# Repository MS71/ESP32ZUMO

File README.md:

# ESP32ZUMO
Small robot based on ESP32 + ROS + ZUMO 32u4 base

Components:
* ZUMO32U4 Base (I2C Slave, Bat ADC, Motor Encoder, PWM for Lidar Stepper, l3gd20h, lsm303d, Line Sonsor, ...)
* ESP32 with PSRAM
* STM vl53l1x TOF sensor
* Rotating Lidar with PCF8475+ULN2003 Stepper motor
* BNO055 Orientation Sensor
* SSD1306 I2C Display

Target Software:
* ROS Serial ported to ESP32

Host Software:
* ROS Bringup Files
* Mapping, Laser Scan, Navigation, ...

Goals:
* Small Autonomous Robot controlled by ROS from external PC
* Small Autonomous Robot controlled by ROS running on ESP32

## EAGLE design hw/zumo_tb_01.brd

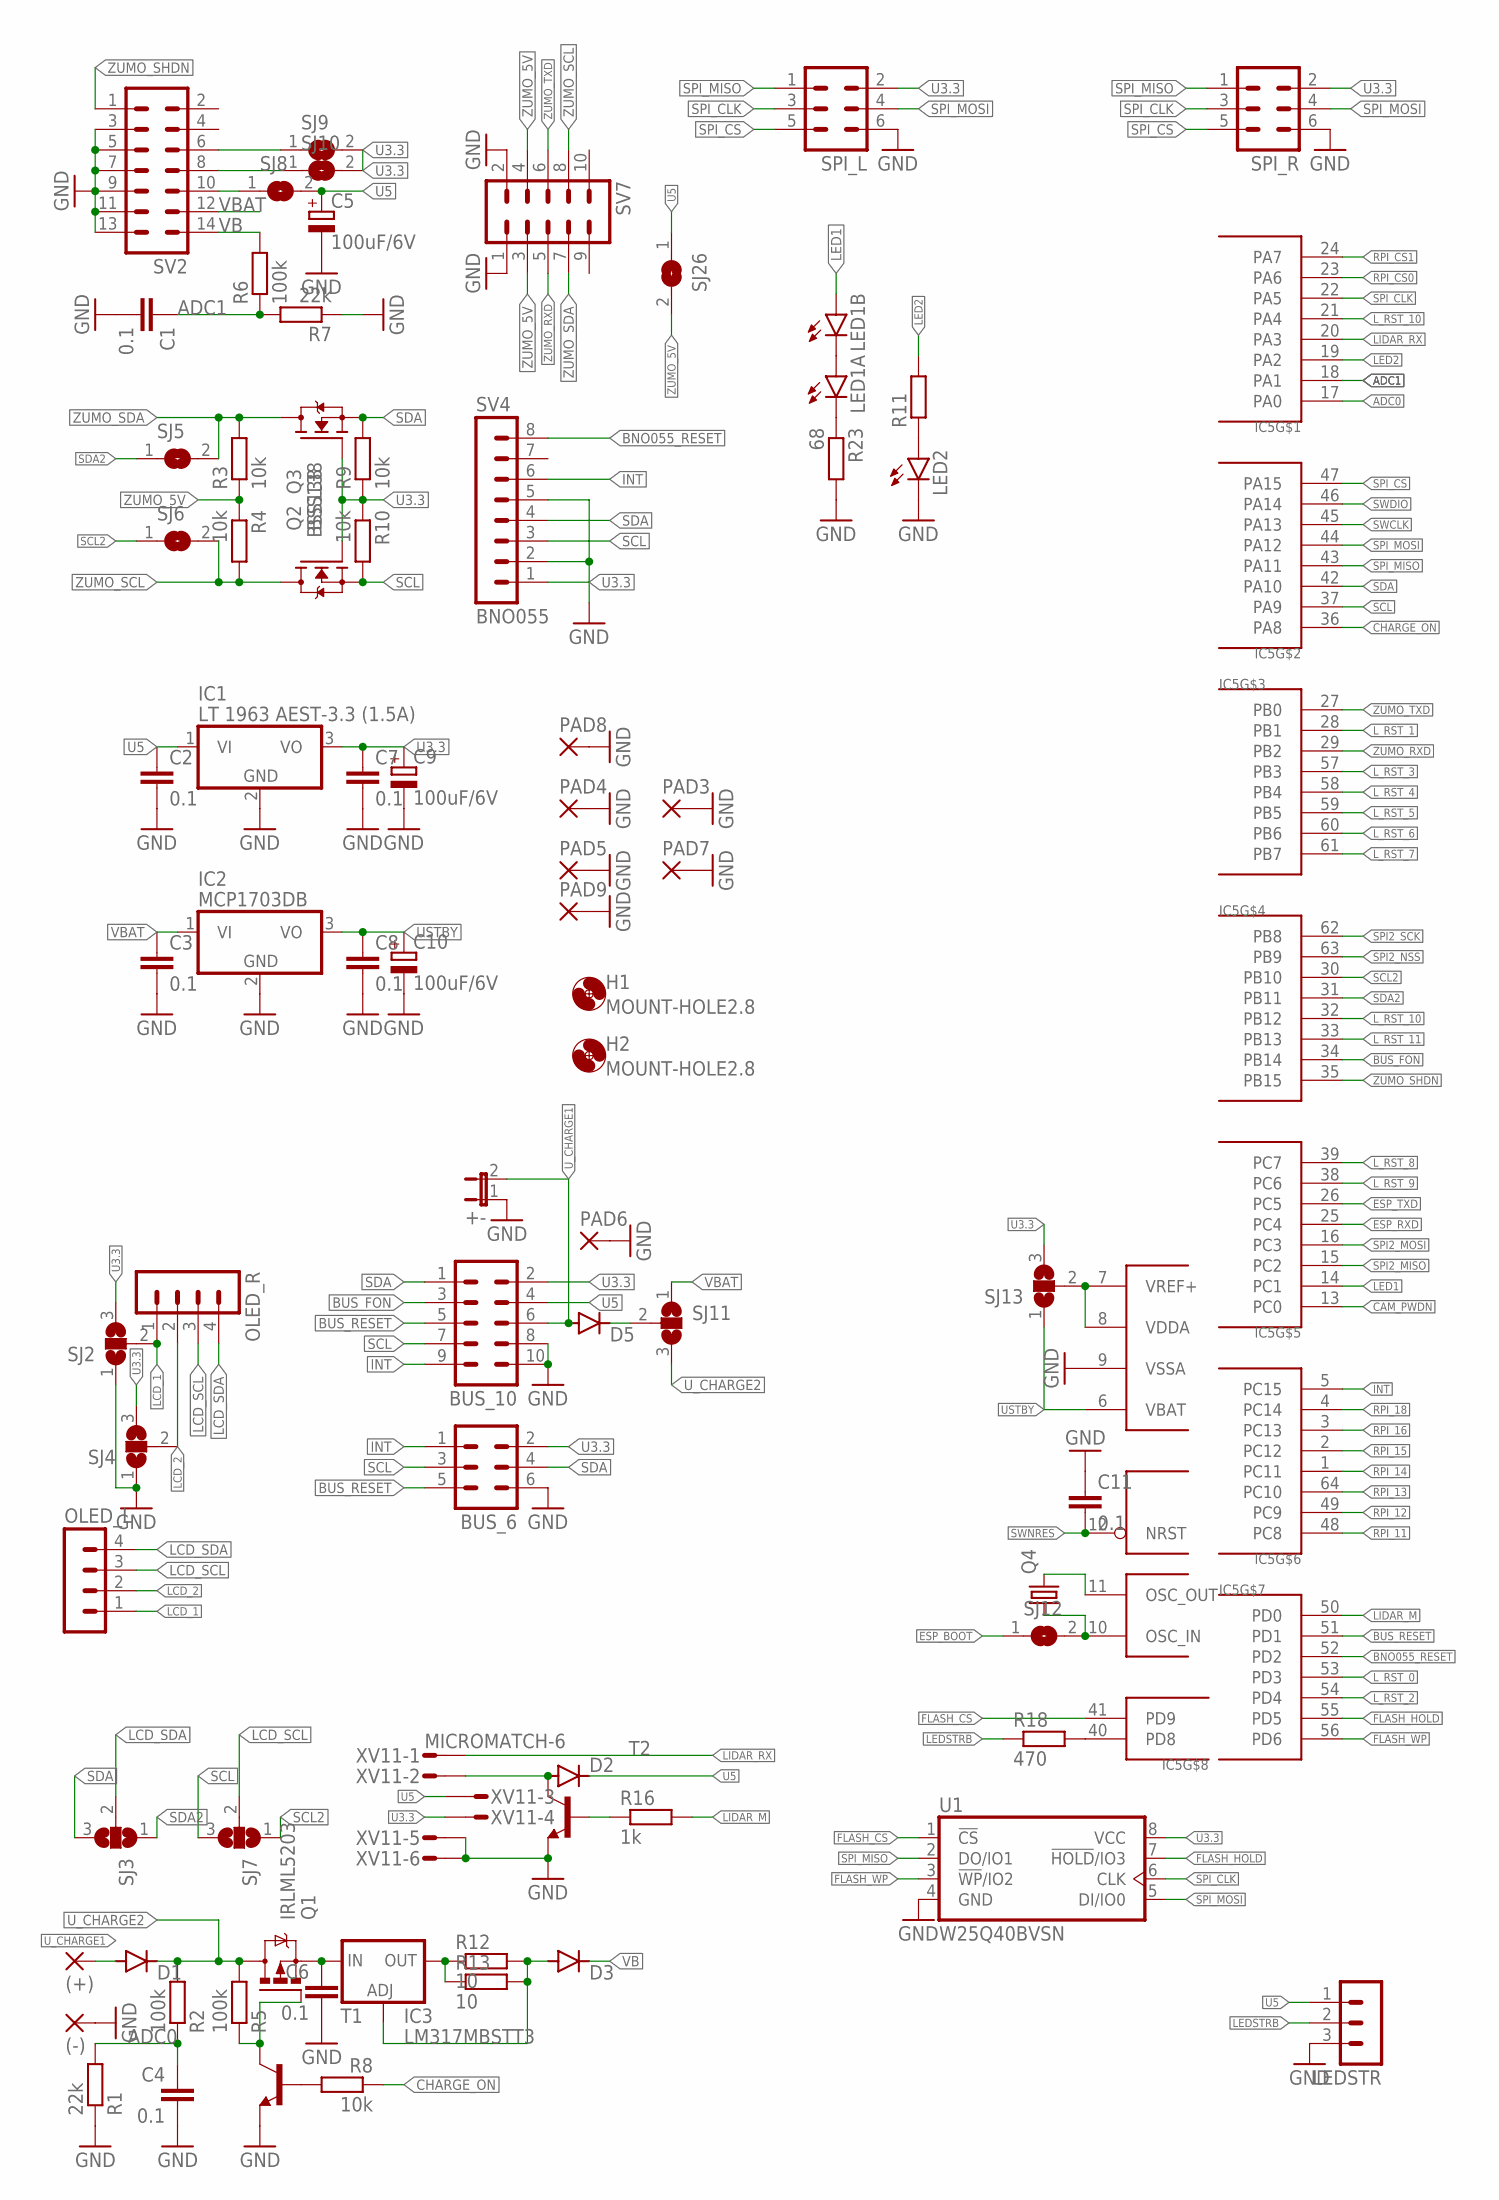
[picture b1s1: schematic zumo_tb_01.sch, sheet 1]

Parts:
(+): 3,81/1,4
(-): 3,81/1,4
+-: JP1E; JP1
BUS_6: ML6
BUS_10: ML10
C1, C2, C3, C4, C6, C7, C8, C11: 0.1; C0805
C5, C9, C10: 100uF/6V; B/3528-21R
D1, D3, D5: DIODE-MELF-MLL41; MELF-MLL41
D2: DIODE-MINIMELF; MINIMELF
H1, H2: MOUNT-HOLE2.8; 2,8
IC1: LT 1963 AEST-3.3 (1.5A); SOT223
IC2: MCP1703DB; SOT223
IC3: LM317MBSTT3; SOT223
IC5: STM32G081RBT6; TQFP64
LED1A, LED1B: LED5MM
LED2: LEDCHIPLED_0805; CHIPLED_0805
LEDSTR: MA03-1
OLED_L: MA04-1
OLED_R: MA04-1
PAD3, PAD7, PAD9: 3,81/1,4
PAD4, PAD5, PAD6, PAD8: 2,15/1,0
Q1: IRLML5203; MICRO3
Q2, Q3: BSS138; SOT23
Q4: CRYSTALTC26V; TC26V
R1, R7: 22k; R0805
R2, R5, R6: 100k; R0805
R3, R4, R8, R9, R10: 10k; R0805
R11: R-EU_R0603; R0603
R12, R13: 10; R2010
R16: 1k; R0805
R18: 470; R0805
R23: 68; R0805
SJ2, SJ3, SJ4, SJ7, SJ11, SJ13: SJ2W; SJ_2
SJ5, SJ6, SJ8, SJ9, SJ10, SJ12, SJ26: SJ
SPI_L: ML6
SPI_R: ML6
SV2: MA07-2
SV4: BNO055; MA08-1
SV7: MA05-2
T1, T2: BC817-16-NPN-SOT23-BEC; SOT23-BEC
U1: W25Q40BVSN; SO08
XV11: MICROMATCH-6

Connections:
ADC0: C4.1, IC5.17 (PA0), R1.2, R2.1
ADC1: C1.1, IC5.18 (PA1), R6.1, R7.2
BNO055_RESET: IC5.52 (PD2), SV4.8
BUS_FON: BUS_10.3, IC5.34 (PB14)
BUS_RESET: BUS_6.5, BUS_10.5, IC5.51 (PD1)
CAM_PWDN: IC5.13 (PC0); also elsewhere on the board
CHARGE_ON: IC5.36 (PA8), R8.1
ESP_BOOT: SJ12.1; also elsewhere on the board
ESP_RXD: IC5.25 (PC4); also elsewhere on the board
ESP_TXD: IC5.26 (PC5); also elsewhere on the board
FLASH_CS: IC5.41 (PD9), U1.1 (!CS!)
FLASH_HOLD: IC5.55 (PD5), U1.7 (!HOLD!/IO3)
FLASH_WP: IC5.56 (PD6), U1.3 (!WP!/IO2)
GND: (-).1, +-.1, BUS_6.6, BUS_10.8, BUS_10.10, C1.2, C2.2, C3.2, C4.2, C5.-, C6.2, C7.2, C8.2, C9.-, C10.-, C11.1, IC1.2 (GND), IC2.2 (GND), IC5.9 (VSSA), LED2.C, LEDSTR.3, PAD3.1, PAD4.1, PAD5.1, PAD6.1, PAD7.1, PAD8.1, PAD9.1, R1.1, R7.1, R23.2, SJ2.1, SJ4.1, SPI_L.6, SPI_R.6, SV2.3, SV2.5, SV2.7, SV2.9, SV2.11, SV2.13, SV4.2, SV4.5, SV7.1, SV7.2, T1.E, T2.E, U1.4 (GND), XV11.5, XV11.6; also elsewhere on the board
INT: BUS_6.1, BUS_10.9, IC5.5 (PC15), SV4.6; also elsewhere on the board
LCD_1: OLED_L.1, OLED_R.1, SJ2.2
LCD_2: OLED_L.2, OLED_R.2, SJ4.2
LCD_SCL: OLED_L.3, OLED_R.3, SJ7.2
LCD_SDA: OLED_L.4, OLED_R.4, SJ3.2
LED1: IC5.14 (PC1), LED1B.A
LED2: IC5.19 (PA2), R11.2
LEDSTRB: LEDSTR.2, R18.1
LIDAR_M: IC5.50 (PD0), R16.2
LIDAR_RX: IC5.20 (PA3), XV11.1
L_RST_0: IC5.53 (PD3); also elsewhere on the board
L_RST_1: IC5.28 (PB1); also elsewhere on the board
L_RST_2: IC5.54 (PD4); also elsewhere on the board
L_RST_3: IC5.57 (PB3); also elsewhere on the board
L_RST_4: IC5.58 (PB4); also elsewhere on the board
L_RST_5: IC5.59 (PB5); also elsewhere on the board
L_RST_6: IC5.60 (PB6); also elsewhere on the board
L_RST_7: IC5.61 (PB7); also elsewhere on the board
L_RST_8: IC5.39 (PC7); also elsewhere on the board
L_RST_9: IC5.38 (PC6); also elsewhere on the board
L_RST_10: IC5.21 (PA4), IC5.32 (PB12); also elsewhere on the board
L_RST_11: IC5.33 (PB13); also elsewhere on the board
unnamed: IC3.4 (OUT), R12.1, R13.1
unnamed: IC5.11 (OSC_OUT), Q4.2
unnamed: IC5.10 (OSC_IN), Q4.1, SJ12.2
unnamed: IC5.40 (PD8), R18.2
unnamed: IC5.7 (VREF+), IC5.8 (VDDA), SJ13.2
unnamed: LED2.A, R11.1
unnamed: SJ10.1, SV2.8
unnamed: SJ9.1, SV2.6
unnamed: D3.A, IC3.1 (ADJ), R12.2, R13.2
unnamed: C6.1, IC3.3 (IN), Q1.2 (S)
unnamed: Q1.1 (G), R5.1, T1.C
unnamed: R8.2, T1.B
unnamed: R16.1, T2.B
unnamed: D5.C, SJ11.2
unnamed: LED1A.A, LED1B.K (C)
unnamed: LED1A.K (C), R23.1
unnamed: D2.A, T2.C, XV11.2
RPI_11: IC5.48 (PC8); also elsewhere on the board
RPI_12: IC5.49 (PC9); also elsewhere on the board
RPI_13: IC5.64 (PC10); also elsewhere on the board
RPI_14: IC5.1 (PC11); also elsewhere on the board
RPI_15: IC5.2 (PC12); also elsewhere on the board
RPI_16: IC5.3 (PC13); also elsewhere on the board
RPI_18: IC5.4 (PC14); also elsewhere on the board
RPI_CS0: IC5.23 (PA6); also elsewhere on the board
RPI_CS1: IC5.24 (PA7); also elsewhere on the board
SCL: BUS_6.3, BUS_10.7, IC5.37 (PA9), Q3.2 (S), R10.2, SJ7.3, SV4.3; also elsewhere on the board
SCL2: IC5.30 (PB10), SJ6.1, SJ7.1
SDA: BUS_6.4, BUS_10.1, IC5.42 (PA10), Q2.2 (S), R9.2, SJ3.3, SV4.4; also elsewhere on the board
SDA2: IC5.31 (PB11), SJ3.1, SJ5.1
SPI2_MISO: IC5.15 (PC2); also elsewhere on the board
SPI2_MOSI: IC5.16 (PC3); also elsewhere on the board
SPI2_NSS: IC5.63 (PB9); also elsewhere on the board
SPI2_SCK: IC5.62 (PB8); also elsewhere on the board
SPI_CLK: IC5.22 (PA5), SPI_L.3, SPI_R.3, U1.6 (CLK); also elsewhere on the board
SPI_CS: IC5.47 (PA15), SPI_L.5, SPI_R.5; also elsewhere on the board
SPI_MISO: IC5.43 (PA11), SPI_L.1, SPI_R.1, U1.2 (DO/IO1); also elsewhere on the board
SPI_MOSI: IC5.44 (PA12), SPI_L.4, SPI_R.4, U1.5 (DI/IO0); also elsewhere on the board
SWCLK: IC5.45 (PA13); also elsewhere on the board
SWDIO: IC5.46 (PA14); also elsewhere on the board
SWNRES: C11.2, IC5.12 (NRST); also elsewhere on the board
U3.3: BUS_6.2, BUS_10.2, C7.1, C9.+, IC1.3 (VO), Q2.1 (G), Q3.1 (G), R9.1, R10.1, SJ2.3, SJ4.3, SJ9.2, SJ10.2, SJ13.3, SPI_L.2, SPI_R.2, SV4.1, U1.8 (VCC), XV11.4; also elsewhere on the board
U5: BUS_10.4, C2.1, C5.+, D2.C, IC1.1 (VI), LEDSTR.1, SJ8.2, SJ26.1, XV11.3; also elsewhere on the board
USTBY: C8.1, C10.+, IC2.3 (VO), IC5.6 (VBAT), SJ13.1; also elsewhere on the board
U_CHARGE1: (+).1, +-.2, BUS_10.6, D1.A, D5.A
U_CHARGE2: D1.C, Q1.3 (D), R2.2, R5.2, SJ11.3
VB: D3.C, R6.2, SV2.14
VBAT: C3.1, IC2.1 (VI), SJ11.1, SV2.12
ZUMO_5V: R3.1, R4.1, SJ26.2, SV7.3, SV7.4
ZUMO_RXD: IC5.29 (PB2), SV7.5
ZUMO_SCL: Q3.3 (D), R4.2, SJ6.2, SV7.8
ZUMO_SDA: Q2.3 (D), R3.2, SJ5.2, SV7.7
ZUMO_SHDN: IC5.35 (PB15), SV2.1; also elsewhere on the board
ZUMO_TXD: IC5.27 (PB0), SV7.6
ZUMO_VREG: SJ8.1, SV2.10

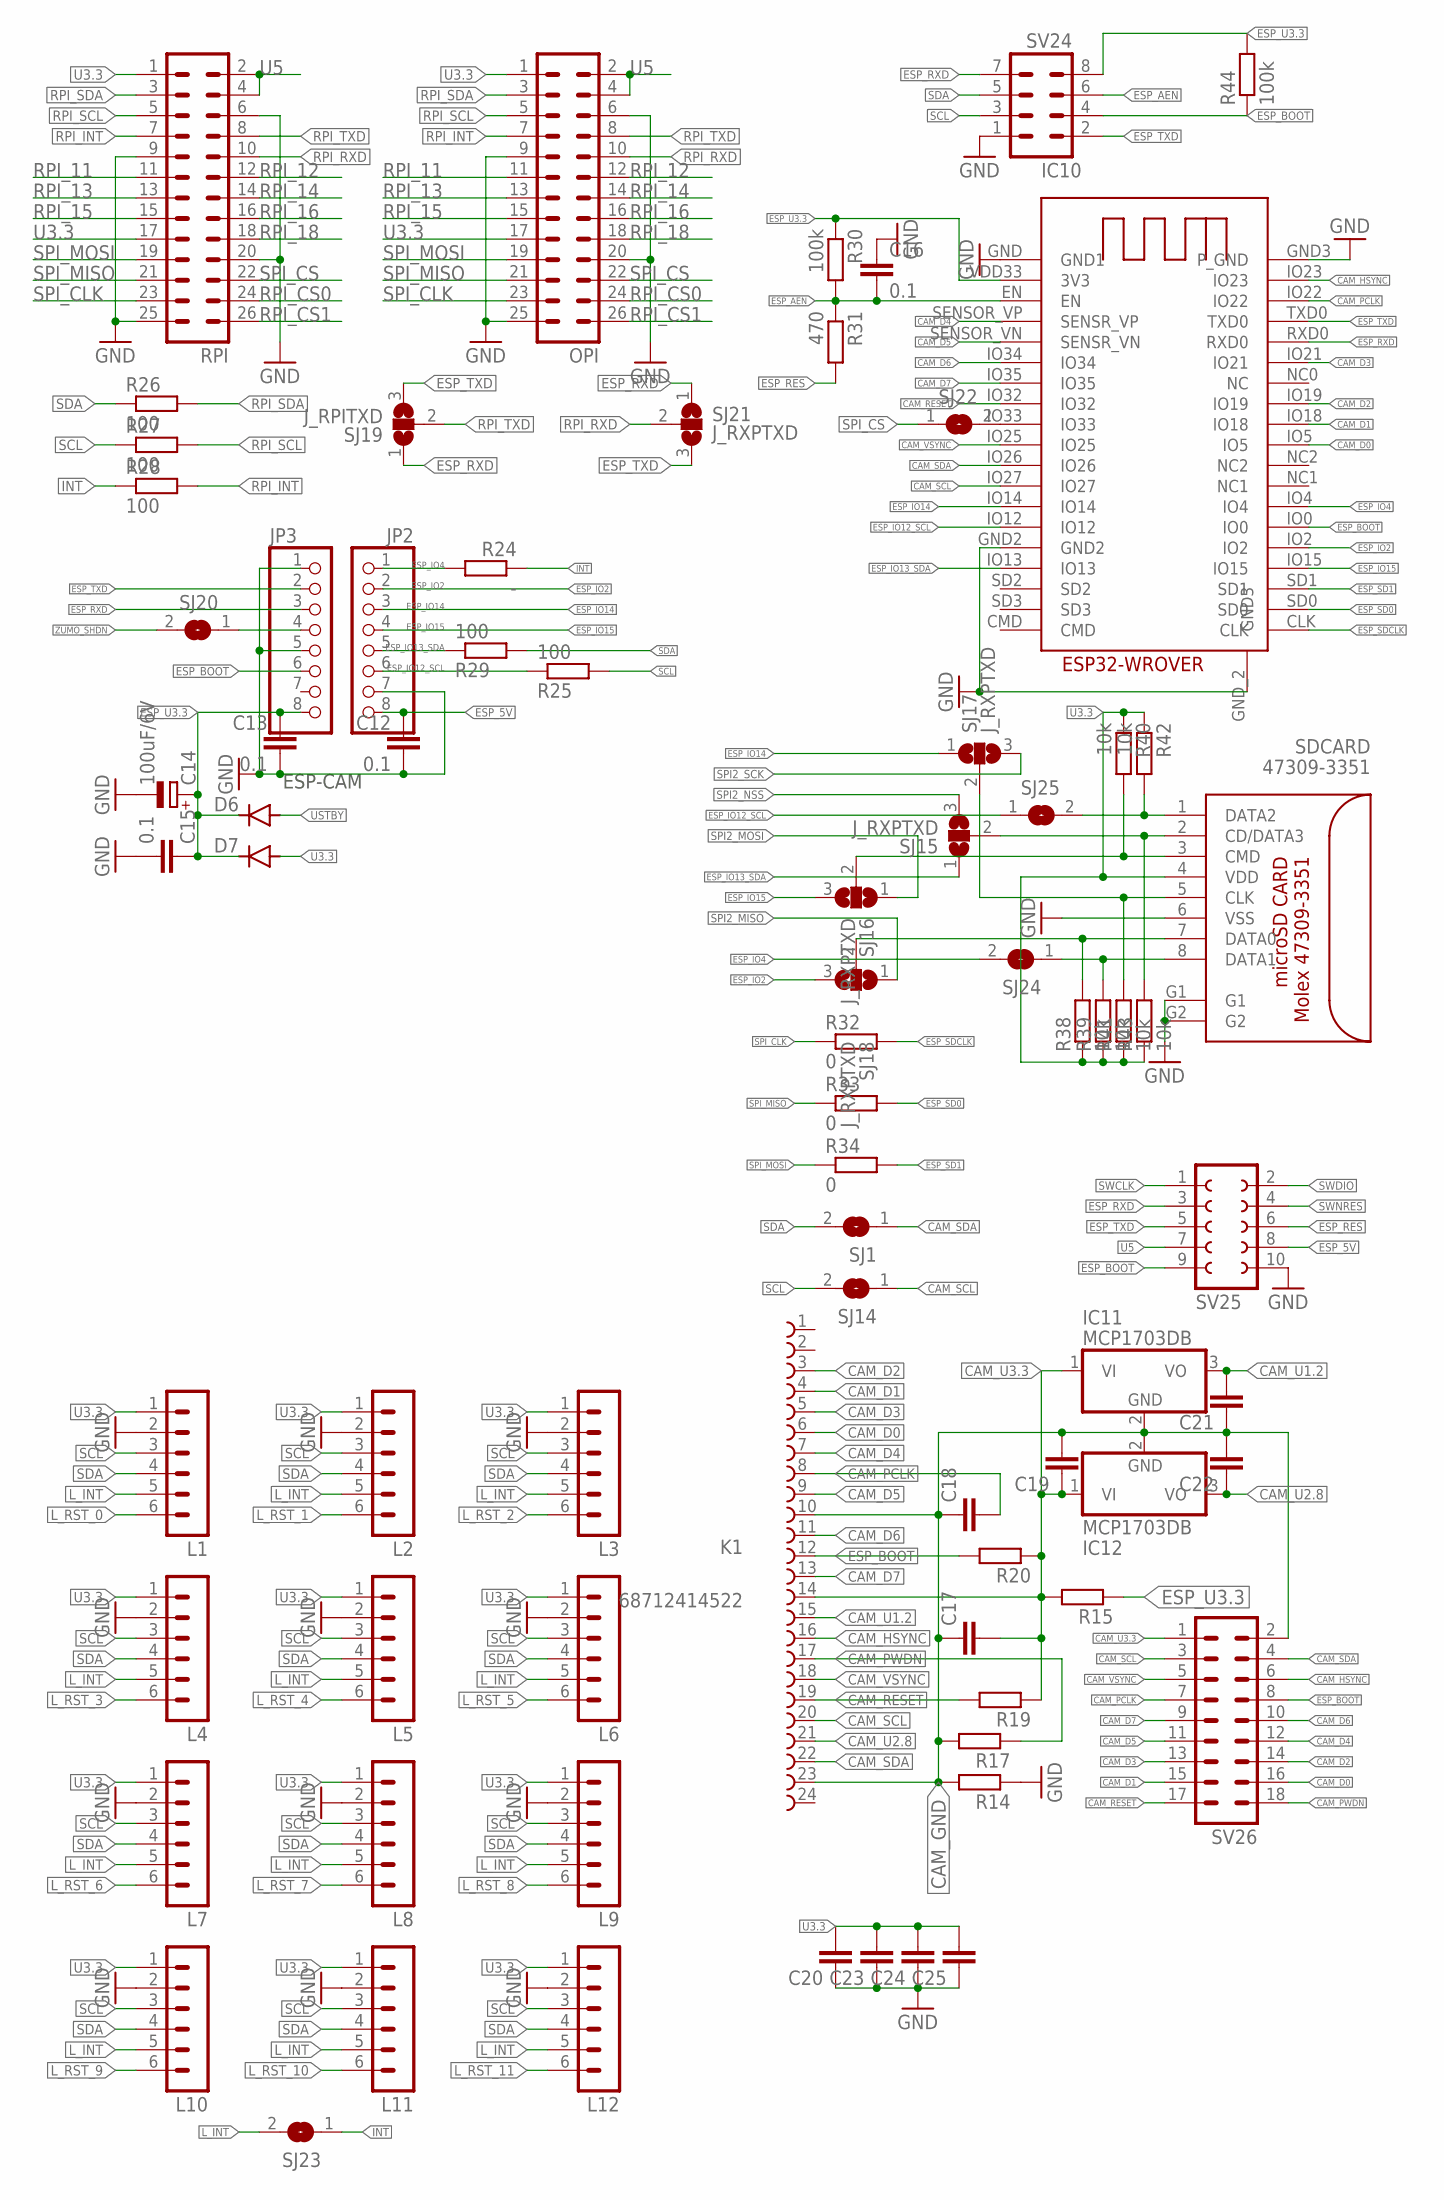
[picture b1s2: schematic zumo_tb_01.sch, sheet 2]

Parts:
C12, C13, C15, C16: 0.1; C0805
C14: 100uF/6V; B/3528-21R
C17, C18, C19, C20, C21, C22, C23, C24, C25: C-EUC0603; C0603
D6, D7: DIODE-MICROMELF-W; MICROMELF-W
IC10: ESP32-WROVER
IC11, IC12: MCP1703DB; SOT223
JP2, JP3: PINHD-1X8_2.54-SMD; 1X08SMD
K1: 68712414522
L1, L2, L3, L4, L5, L6, L7, L8, L9, L10, L11, L12: MA06-1
OPI: MA13-2
R14, R15, R17, R19, R20: R-EU_R0603; R0603
R24: -; R0805
R25, R26, R27, R28, R29: 100; R0805
R30, R44: 100k; R0805
R31: 470; R0805
R32, R33, R34: 0; R0805
R38, R39, R40, R41, R42, R43: 10k; R0805
RPI: MA13-2
SDCARD: 47309-3351
SJ1, SJ14, SJ20, SJ22, SJ23, SJ24, SJ25: SJ
SJ15, SJ16, SJ17, SJ18, SJ21: J_RXPTXD; SJ_2
SJ19: J_RPITXD; SJ_2
SV24: MA04-2
SV25: FE05-2
SV26: MA09-2

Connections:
CAM_D0: IC10.IO5, K1.6, SV26.16
CAM_D1: IC10.IO18, K1.4, SV26.15
CAM_D2: IC10.IO19, K1.3, SV26.14
CAM_D3: IC10.IO21, K1.5, SV26.13
CAM_D4: IC10.SENSOR_VP (SENSR_VP), K1.7, SV26.12
CAM_D5: IC10.SENSOR_VN (SENSR_VN), K1.9, SV26.11
CAM_D6: IC10.IO34, K1.11, SV26.10
CAM_D7: IC10.IO35, K1.13, SV26.9
CAM_GND: C17.1, C18.1, C19.2, C21.1, C22.2, IC11.2 (GND), IC12.2 (GND), K1.10, K1.23, R14.2, R17.2, SV26.2
CAM_HSYNC: IC10.IO23, K1.16, SV26.6
CAM_PCLK: C18.2, IC10.IO22, K1.8, SV26.7
CAM_PWDN: K1.17, R17.1, SV26.18; also elsewhere on the board
CAM_RESET: IC10.IO32, K1.19, R19.2, SV26.17
CAM_SCL: IC10.IO27, K1.20, SJ14.1, SV26.3
CAM_SDA: IC10.IO26, K1.22, SJ1.1, SV26.4
CAM_U1.2: C21.2, IC11.3 (VO), K1.15
CAM_U2.8: C22.1, IC12.3 (VO), K1.21
CAM_U3.3: C17.2, C19.1, IC11.1 (VI), IC12.1 (VI), K1.14, R15.2, R19.1, R20.1, SV26.1
CAM_VSYNC: IC10.IO25, K1.18, SV26.5
ESPCAM_13: JP3.4, SJ20.1
ESP_5V: C12.1, JP2.8, SV25.8
ESP_AEN: C16.2, IC10.EN, R30.2, R31.1, SV24.6
ESP_BOOT: IC10.IO0, JP3.6, K1.12, R20.2, R44.1, SV24.4, SV25.9, SV26.8; also elsewhere on the board
ESP_IO2: IC10.IO2, JP2.2, SJ18.3
ESP_IO4: IC10.IO4, JP2.1, R24.2, SJ24.2
ESP_IO12_SCL: IC10.IO12, JP2.6, R25.1, SJ25.1
ESP_IO13_SDA: IC10.IO13, JP2.5, R29.1, SJ15.1
ESP_IO14: IC10.IO14, JP2.3, SJ17.1
ESP_IO15: IC10.IO15, JP2.4, SJ16.3
ESP_RES: R31.2, SV25.6
ESP_RXD: IC10.RXD0, JP3.3, SJ19.1, SJ21.1, SV24.7, SV25.3; also elsewhere on the board
ESP_SD0: IC10.SD0, R33.2
ESP_SD1: IC10.SD1, R34.2
ESP_SDCLK: IC10.CLK, R32.2
ESP_TXD: IC10.TXD0, JP3.2, SJ19.3, SJ21.3, SV24.2, SV25.5; also elsewhere on the board
ESP_U3.3: C13.1, C14.+, C15.1, D6.C, D7.C, IC10.VDD33 (3V3), JP3.8, R15.1, R30.1, R44.2, SV24.8
GND: C12.2, C13.2, C14.-, C15.2, C16.1, C20.1, C23.1, C24.1, C25.1, IC10.GND (GND1), IC10.GND2, IC10.GND3 (P_GND), IC10.GND_2 (GND3), JP2.7, JP3.1, JP3.5, L1.2, L2.2, L3.2, L4.2, L5.2, L6.2, L7.2, L8.2, L9.2, L10.2, L11.2, L12.2, OPI.6, OPI.9, OPI.20, OPI.25, R14.1, RPI.6, RPI.9, RPI.20, RPI.25, SDCARD.6 (VSS), SDCARD.G1, SDCARD.G2, SV24.1, SV25.10; also elsewhere on the board
INT: R24.1, R28.1, SJ23.1; also elsewhere on the board
L_INT: L1.5, L2.5, L3.5, L4.5, L5.5, L6.5, L7.5, L8.5, L9.5, L10.5, L11.5, L12.5, SJ23.2
L_RST_0: L1.6; also elsewhere on the board
L_RST_1: L2.6; also elsewhere on the board
L_RST_2: L3.6; also elsewhere on the board
L_RST_3: L4.6; also elsewhere on the board
L_RST_4: L5.6; also elsewhere on the board
L_RST_5: L6.6; also elsewhere on the board
L_RST_6: L7.6; also elsewhere on the board
L_RST_7: L8.6; also elsewhere on the board
L_RST_8: L9.6; also elsewhere on the board
L_RST_9: L10.6; also elsewhere on the board
L_RST_10: L11.6; also elsewhere on the board
L_RST_11: L12.6; also elsewhere on the board
unnamed: IC10.IO33, SJ22.2
RPI_11: OPI.11, RPI.11; also elsewhere on the board
RPI_12: OPI.12, RPI.12; also elsewhere on the board
RPI_13: OPI.13, RPI.13; also elsewhere on the board
RPI_14: OPI.14, RPI.14; also elsewhere on the board
RPI_15: OPI.15, RPI.15; also elsewhere on the board
RPI_16: OPI.16, RPI.16; also elsewhere on the board
RPI_18: OPI.18, RPI.18; also elsewhere on the board
RPI_CS0: OPI.24, RPI.24; also elsewhere on the board
RPI_CS1: OPI.26, RPI.26; also elsewhere on the board
RPI_INT: OPI.7, R28.2, RPI.7
RPI_RXD: OPI.10, RPI.10, SJ21.2
RPI_SCL: OPI.5, R27.2, RPI.5
RPI_SDA: OPI.3, R26.2, RPI.3
RPI_TXD: OPI.8, RPI.8, SJ19.2
SCL: L1.3, L2.3, L3.3, L4.3, L5.3, L6.3, L7.3, L8.3, L9.3, L10.3, L11.3, L12.3, R25.2, R27.1, SJ14.2, SV24.3; also elsewhere on the board
SDA: L1.4, L2.4, L3.4, L4.4, L5.4, L6.4, L7.4, L8.4, L9.4, L10.4, L11.4, L12.4, R26.1, R29.2, SJ1.2, SV24.5; also elsewhere on the board
SD_CLK: R41.2, SDCARD.5 (CLK), SJ17.2
SD_CMD: R40.2, SDCARD.3 (CMD), SJ16.2
SD_DAT0: R38.2, SDCARD.7 (DATA0), SJ18.2
SD_DAT1: R39.2, SDCARD.8 (DATA1), SJ24.1
SD_DAT2: R42.2, SDCARD.1 (DATA2), SJ25.2
SD_DAT3: R43.2, SDCARD.2 (CD/DATA3), SJ15.2
SPI2_MISO: SJ18.1; also elsewhere on the board
SPI2_MOSI: SJ16.1; also elsewhere on the board
SPI2_NSS: SJ15.3; also elsewhere on the board
SPI2_SCK: SJ17.3; also elsewhere on the board
SPI_CLK: OPI.23, R32.1, RPI.23; also elsewhere on the board
SPI_CS: OPI.22, RPI.22, SJ22.1; also elsewhere on the board
SPI_MISO: OPI.21, R33.1, RPI.21; also elsewhere on the board
SPI_MOSI: OPI.19, R34.1, RPI.19; also elsewhere on the board
SWCLK: SV25.1; also elsewhere on the board
SWDIO: SV25.2; also elsewhere on the board
SWNRES: SV25.4; also elsewhere on the board
U3.3: C20.2, C23.2, C24.2, C25.2, D7.A, L1.1, L2.1, L3.1, L4.1, L5.1, L6.1, L7.1, L8.1, L9.1, L10.1, L11.1, L12.1, OPI.1, OPI.17, R38.1, R39.1, R40.1, R41.1, R42.1, R43.1, RPI.1, RPI.17, SDCARD.4 (VDD); also elsewhere on the board
U5: OPI.2, OPI.4, RPI.2, RPI.4, SV25.7; also elsewhere on the board
USTBY: D6.A; also elsewhere on the board
ZUMO_SHDN: SJ20.2; also elsewhere on the board

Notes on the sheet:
ESP-CAM

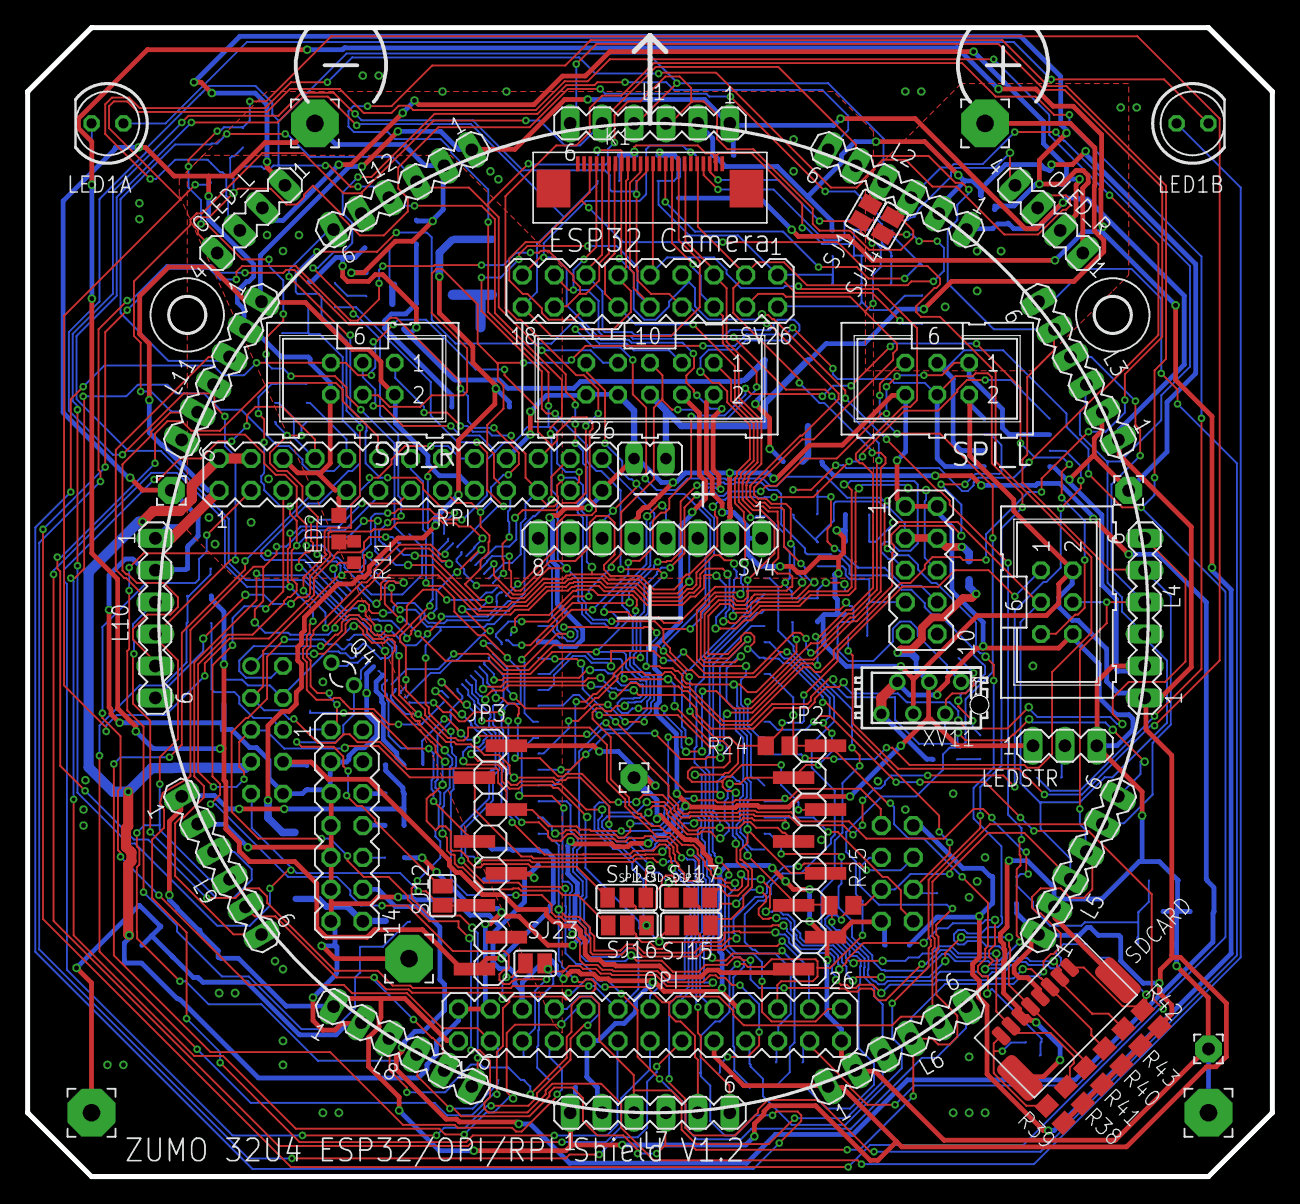
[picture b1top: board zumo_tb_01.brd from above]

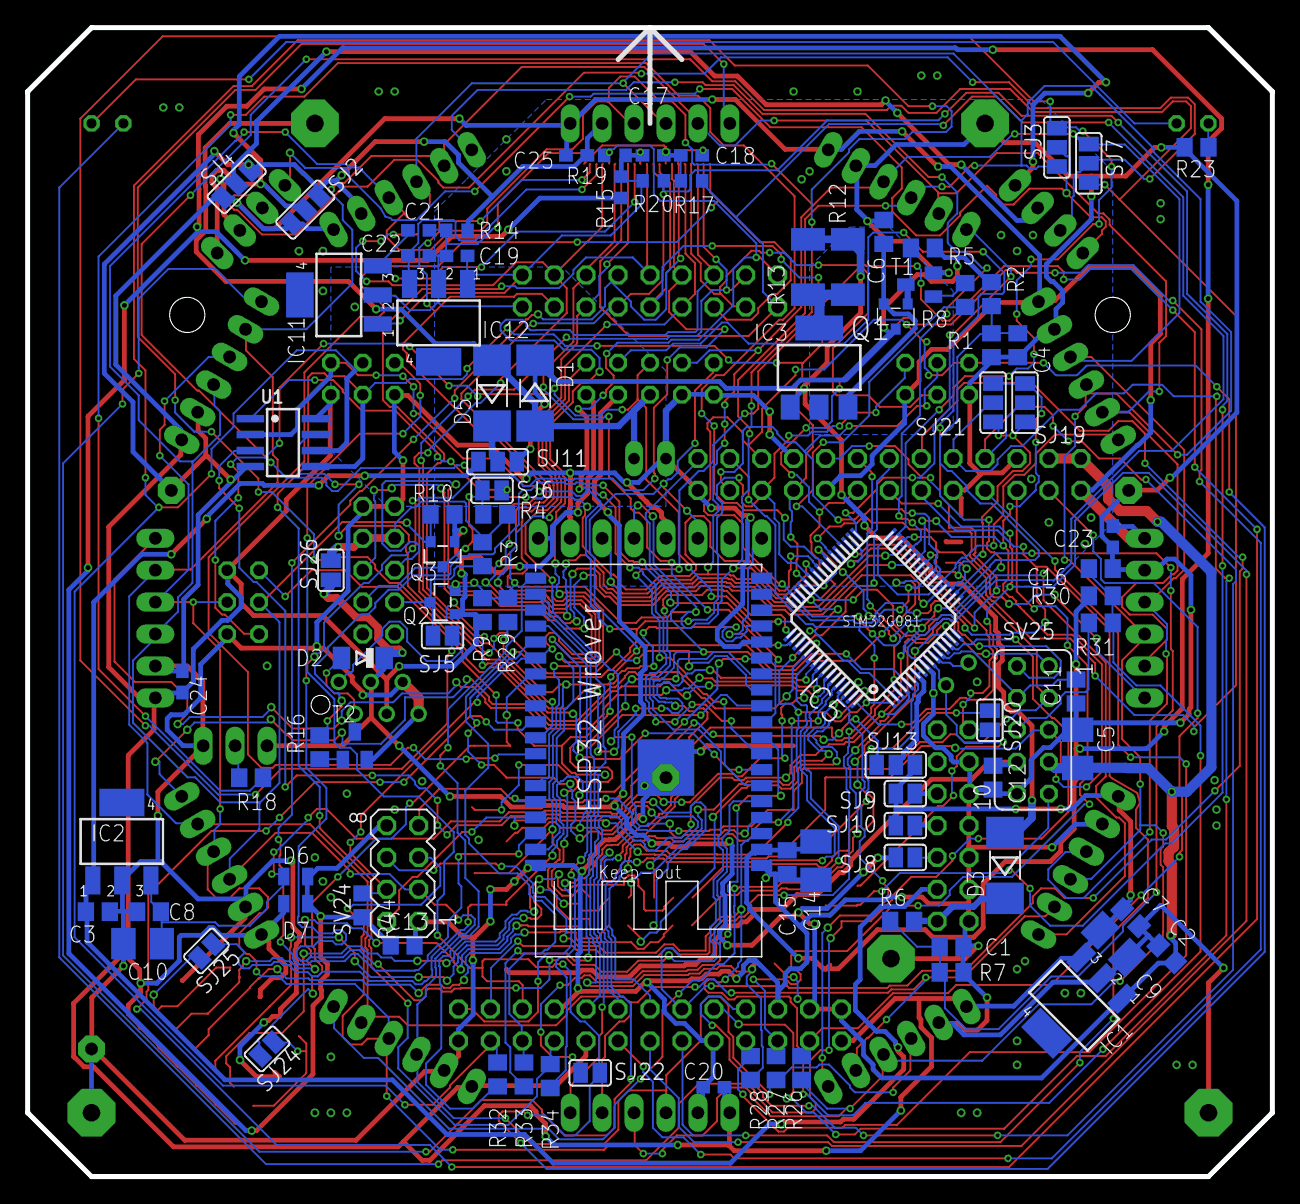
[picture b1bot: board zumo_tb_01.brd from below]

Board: 2 copper layers, 99.1 x 91.4 mm, 157 parts (94 on the bottom side), 136 nets.

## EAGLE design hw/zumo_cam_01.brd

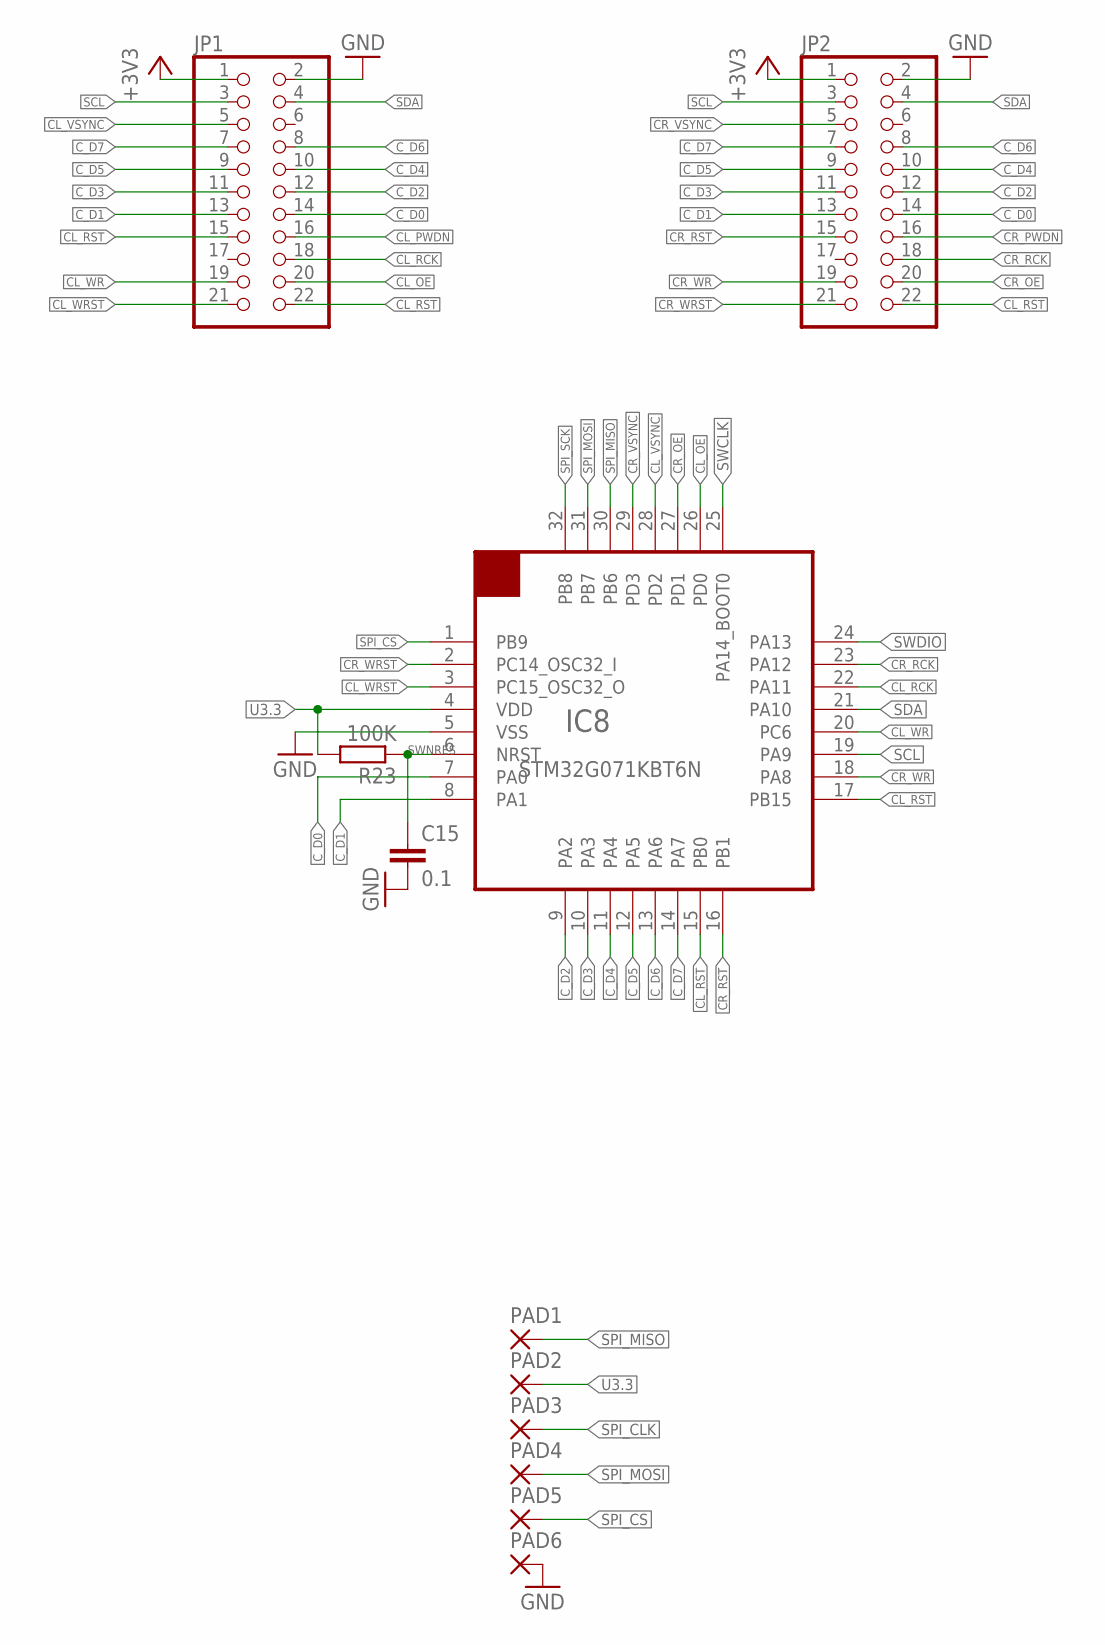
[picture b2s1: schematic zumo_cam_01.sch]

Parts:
C15: 0.1; C0805
IC8: STM32G071KBT6N; LQFP-32
JP1, JP2: PINHD-2X11_2.54-SMD; 2X11SMD
PAD1, PAD2, PAD3, PAD4, PAD5, PAD6: SMD2; SMD1,27-2,54
R23: 100K; R0805

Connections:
+3V3: JP1.1, JP2.1
CL_OE: IC8.26 (PD0), JP1.20
CL_PWDN: JP1.16
CL_RCK: IC8.22 (PA11), JP1.18
CL_RST: IC8.15 (PB0), IC8.17 (PB15), JP1.15, JP1.22, JP2.22
CL_VSYNC: IC8.28 (PD2), JP1.5
CL_WR: IC8.20 (PC6), JP1.19
CL_WRST: IC8.3 (PC15_OSC32_O), JP1.21
CR_OE: IC8.27 (PD1), JP2.20
CR_PWDN: JP2.16
CR_RCK: IC8.23 (PA12), JP2.18
CR_RST: IC8.16 (PB1), JP2.15
CR_VSYNC: IC8.29 (PD3), JP2.5
CR_WR: IC8.18 (PA8), JP2.19
CR_WRST: IC8.2 (PC14_OSC32_I), JP2.21
C_D0: IC8.7 (PA0), JP1.14, JP2.14
C_D1: IC8.8 (PA1), JP1.13, JP2.13
C_D2: IC8.9 (PA2), JP1.12, JP2.12
C_D3: IC8.10 (PA3), JP1.11, JP2.11
C_D4: IC8.11 (PA4), JP1.10, JP2.10
C_D5: IC8.12 (PA5), JP1.9, JP2.9
C_D6: IC8.13 (PA6), JP1.8, JP2.8
C_D7: IC8.14 (PA7), JP1.7, JP2.7
GND: C15.2, IC8.5 (VSS), JP1.2, JP2.2, PAD6.1
SCL: IC8.19 (PA9), JP1.3, JP2.3
SDA: IC8.21 (PA10), JP1.4, JP2.4
SPI_CLK: PAD3.1
SPI_CS: IC8.1 (PB9), PAD5.1
SPI_MISO: IC8.30 (PB6), PAD1.1
SPI_MOSI: IC8.31 (PB7), PAD4.1
SPI_SCK: IC8.32 (PB8)
SWCLK: IC8.25 (PA14_BOOT0)
SWDIO: IC8.24 (PA13)
SWNRES: C15.1, IC8.6 (NRST), R23.1
U3.3: IC8.4 (VDD), PAD2.1, R23.2

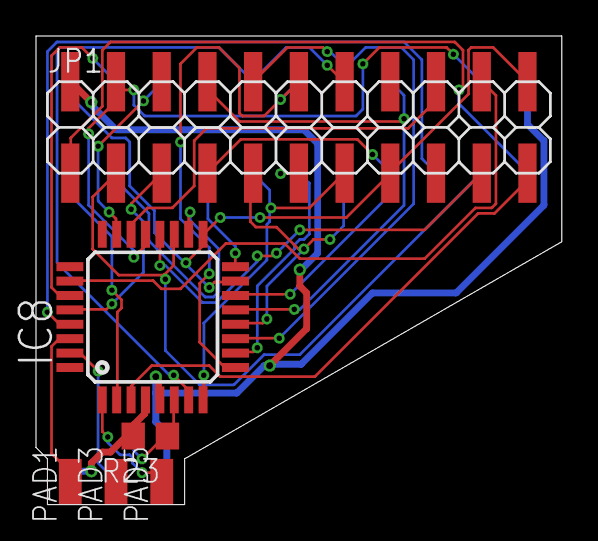
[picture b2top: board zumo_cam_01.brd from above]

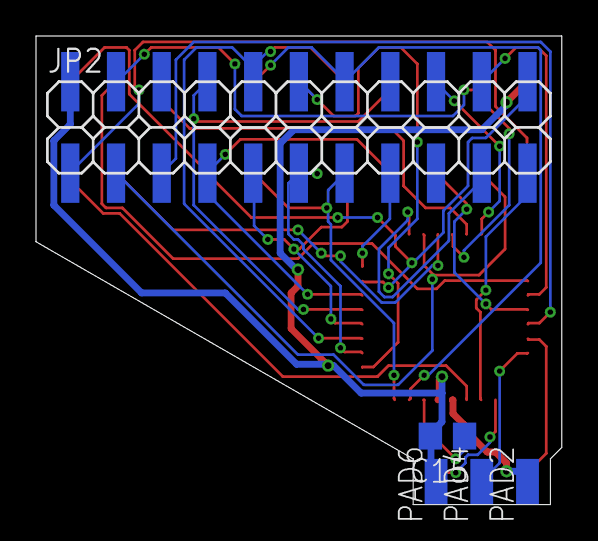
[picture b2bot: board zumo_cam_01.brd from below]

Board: 2 copper layers, 29.2 x 26.0 mm, 11 parts (5 on the bottom side), 29 nets.

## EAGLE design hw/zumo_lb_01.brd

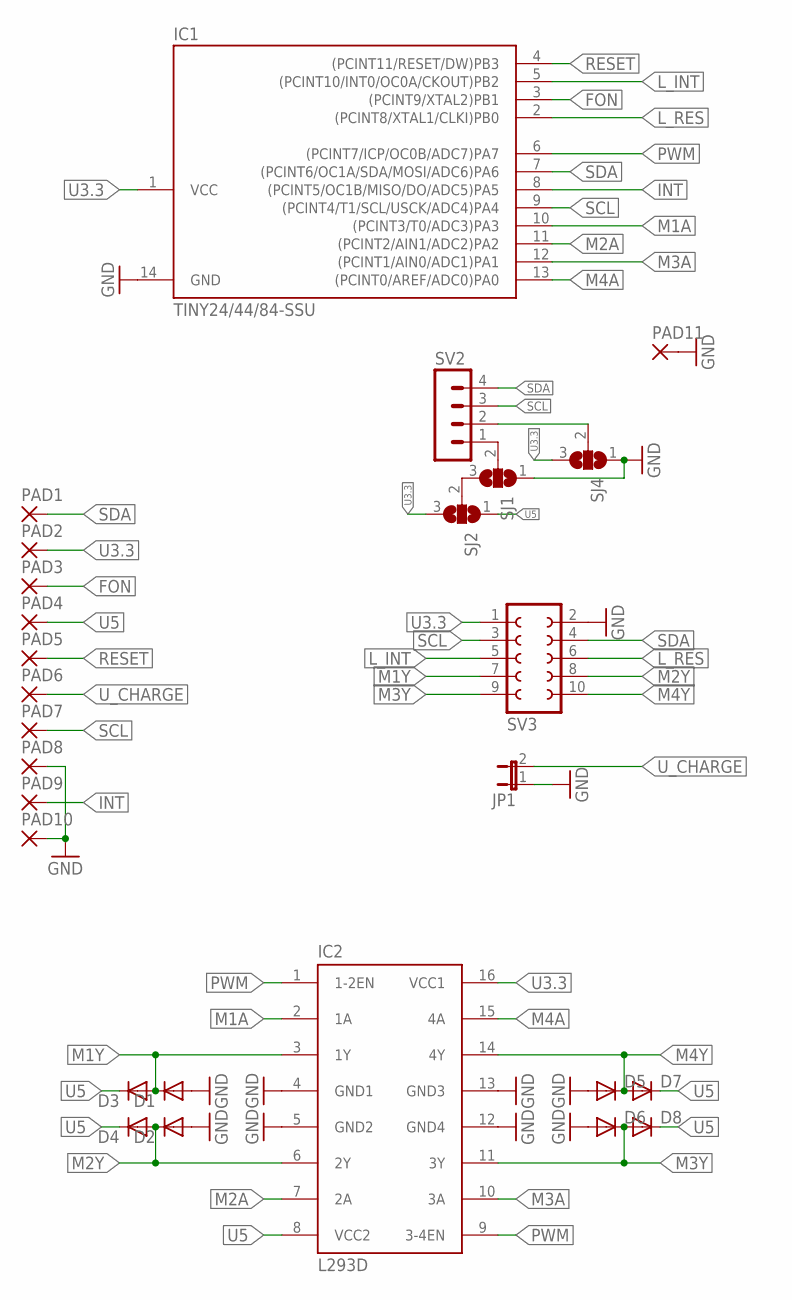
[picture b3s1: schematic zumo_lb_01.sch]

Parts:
D1, D2, D3, D4, D5, D6, D7, D8: DIODE-MINIMELF; MINIMELF
IC1: TINY24/44/84-SSU; SOIC14
IC2: L293D; DIL16
JP1: JP1E; JP1
PAD1, PAD2, PAD3, PAD4, PAD5, PAD6, PAD7, PAD8, PAD9, PAD10: SMD2; SMD1,27-2,54
PAD11: 3,81/1,4
SJ1, SJ2, SJ4: SJ2W; SJ_2
SV2: MA04-1
SV3: FE05-2

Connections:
FON: IC1.3 ((PCINT9/XTAL2)PB1), PAD3.1
GND: D1.A, D2.A, D5.A, D6.A, IC1.14 (GND), IC2.4 (GND1), IC2.5 (GND2), IC2.12 (GND4), IC2.13 (GND3), JP1.1, PAD8.1, PAD10.1, PAD11.1, SJ1.1, SJ4.1, SV3.2
INT: IC1.8 ((PCINT5/OC1B/MISO/DO/ADC5)PA5), PAD9.1
LCD_1: SJ1.2, SV2.1
LCD_2: SJ4.2, SV2.2
L_INT: IC1.5 ((PCINT10/INT0/OC0A/CKOUT)PB2), SV3.5
L_RES: IC1.2 ((PCINT8/XTAL1/CLKI)PB0), SV3.6
M1A: IC1.10 ((PCINT3/T0/ADC3)PA3), IC2.2 (1A)
M1Y: D1.C, D3.A, IC2.3 (1Y), SV3.7
M2A: IC1.11 ((PCINT2/AIN1/ADC2)PA2), IC2.7 (2A)
M2Y: D2.C, D4.A, IC2.6 (2Y), SV3.8
M3A: IC1.12 ((PCINT1/AIN0/ADC1)PA1), IC2.10 (3A)
M3Y: D6.C, D8.A, IC2.11 (3Y), SV3.9
M4A: IC1.13 ((PCINT0/AREF/ADC0)PA0), IC2.15 (4A)
M4Y: D5.C, D7.A, IC2.14 (4Y), SV3.10
unnamed: SJ1.3, SJ2.2
PWM: IC1.6 ((PCINT7/ICP/OC0B/ADC7)PA7), IC2.1 (1-2EN), IC2.9 (3-4EN)
RESET: IC1.4 ((PCINT11/RESET/DW)PB3), PAD5.1
SCL: IC1.9 ((PCINT4/T1/SCL/USCK/ADC4)PA4), PAD7.1, SV2.3, SV3.3
SDA: IC1.7 ((PCINT6/OC1A/SDA/MOSI/ADC6)PA6), PAD1.1, SV2.4, SV3.4
U3.3: IC1.1 (VCC), IC2.16 (VCC1), PAD2.1, SJ2.3, SJ4.3, SV3.1
U5: D3.C, D4.C, D7.C, D8.C, IC2.8 (VCC2), PAD4.1, SJ2.1
U_CHARGE: JP1.2, PAD6.1

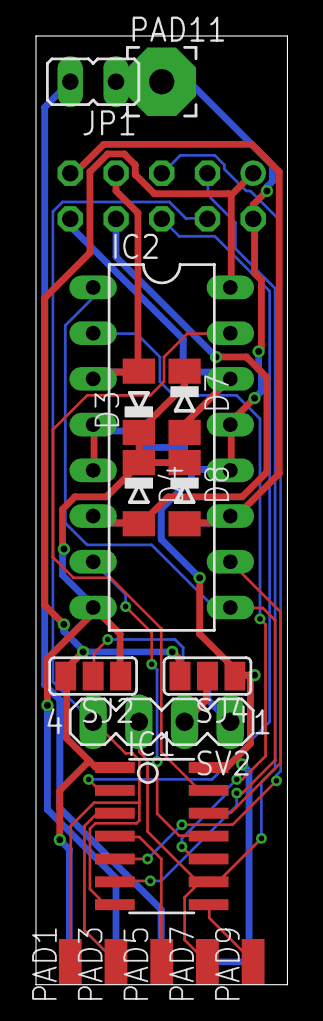
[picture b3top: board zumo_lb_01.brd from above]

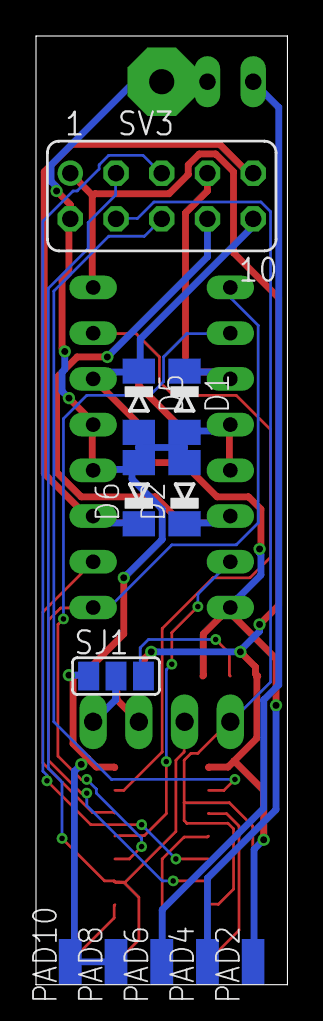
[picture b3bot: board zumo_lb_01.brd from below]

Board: 2 copper layers, 14.0 x 52.7 mm, 27 parts (11 on the bottom side), 23 nets.

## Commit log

2019-03-14 added
2019-03-14 resized
2019-04-05 some small issues fixed
2019-04-05 configuration improved
2019-04-07 first navigation was possible
2019-04-07 some improvements
2019-04-07 parameter optimized
2019-04-07 pid added
2019-04-08 pid implemented
2019-04-09 imu issue fixed
2019-04-09 problem with imu fixed
2019-04-19 zumo ranger sensor added
2019-04-26 lidar range changed and many other parameters changed

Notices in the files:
parts and their libraries:
FPC_Connectors_Flat_Flexible_Cable_rev15: Copyright: Würth Elektronik
memory-winbond: Copyright (C) 2010, Bob Starr
